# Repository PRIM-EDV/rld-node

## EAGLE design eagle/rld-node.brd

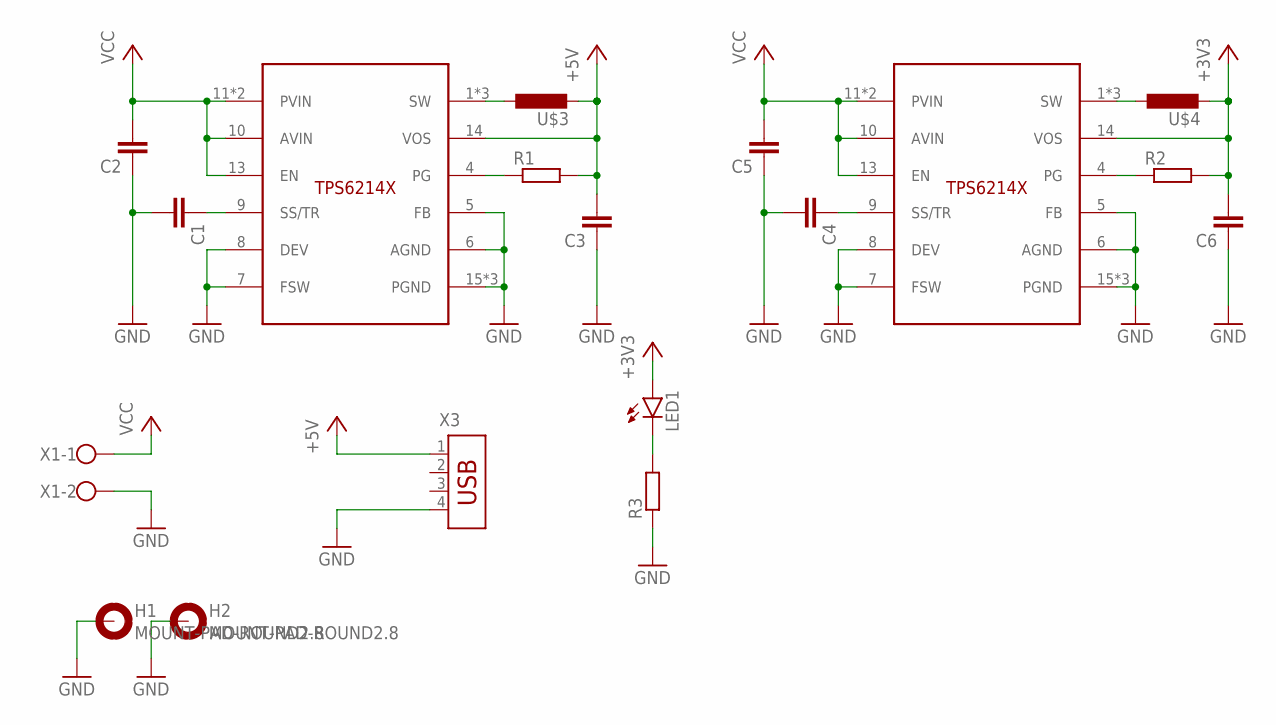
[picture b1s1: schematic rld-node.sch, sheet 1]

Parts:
C1, C2, C3, C4, C5, C6: C-EUC0805; C0805
H1, H2: MOUNT-PAD-ROUND2.8; 2,8-PAD
L1, L2: TPS6214X; VQFN16-3X3
LED1: LEDSML0805; SML0805
R1, R2, R3: R-EU_R0805; R0805
U$3, U$4: IHLP-1212; 1212BZ
X1: W237-102
X3: USB-787616; USB

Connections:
+3V3: C6.2, L2.14 (VOS), LED1.A, R2.2, U$4.2; also elsewhere on the board
+5V: C3.2, L1.14 (VOS), R1.2, U$3.2, X3.1
GND: C1.2, C2.1, C3.1, C4.2, C5.1, C6.1, H1.B2,8, H2.B2,8, L1.5 (FB), L1.6 (AGND), L1.7 (FSW), L1.8 (DEV), L1.15 (PGND), L1.16 (PGND), L1.17 (PGND), L2.5 (FB), L2.6 (AGND), L2.7 (FSW), L2.8 (DEV), L2.15 (PGND), L2.16 (PGND), L2.17 (PGND), R3.1, X1.2, X3.4; also elsewhere on the board
unnamed: C1.1, L1.9 (SS/TR)
unnamed: C4.1, L2.9 (SS/TR)
unnamed: L2.4 (PG), R2.1
unnamed: L1.4 (PG), R1.1
unnamed: L1.1 (SW), L1.2 (SW), L1.3 (SW), U$3.1
unnamed: L2.1 (SW), L2.2 (SW), L2.3 (SW), U$4.1
unnamed: LED1.C, R3.2
VCC: C2.2, C5.2, L1.10 (AVIN), L1.11 (PVIN), L1.12 (PVIN), L1.13 (EN), L2.10 (AVIN), L2.11 (PVIN), L2.12 (PVIN), L2.13 (EN), X1.1

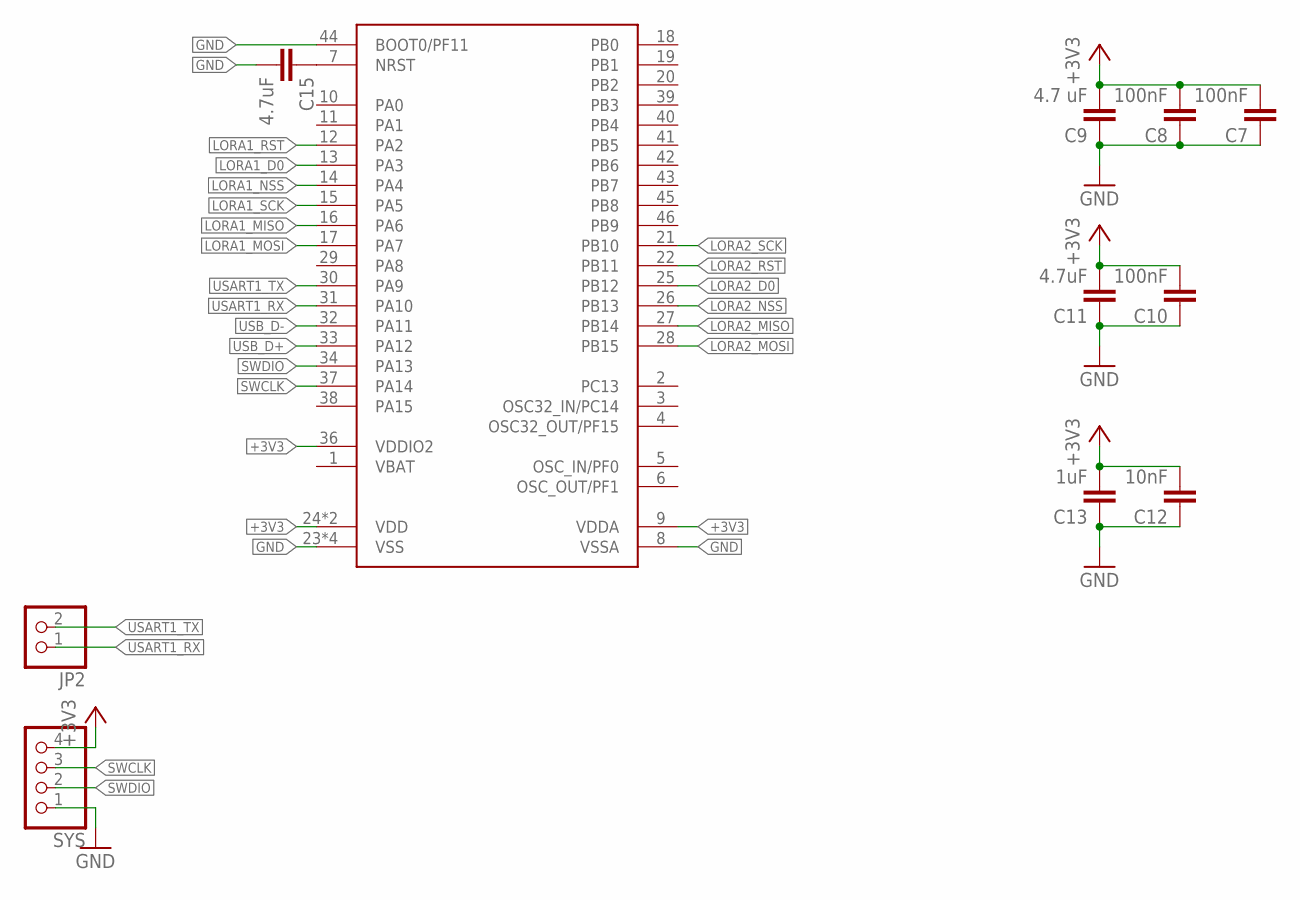
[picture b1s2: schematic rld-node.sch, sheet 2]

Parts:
C7, C8, C10: 100nF; C0805
C9: 4.7 uF; C0805
C11, C15: 4.7uF; C0805
C12: 10nF; C0805
C13: 1uF; C0805
JP2: PINHD-1X2; 1X02
SYS: PINHD-1X4; 1X04
U$5: STM32-F042X4/6-48; UFQFPN48-7X7

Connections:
+3V3: C7.2, C8.2, C9.2, C10.2, C11.2, C12.2, C13.2, SYS.4, U$5.9 (VDDA), U$5.24 (VDD), U$5.36 (VDDIO2), U$5.48 (VDD); also elsewhere on the board
GND: C7.1, C8.1, C9.1, C10.1, C11.1, C12.1, C13.1, C15.2, SYS.1, U$5.8 (VSSA), U$5.23 (VSS), U$5.35 (VSS), U$5.44 (BOOT0/PF11), U$5.47 (VSS), U$5.49 (VSS); also elsewhere on the board
LORA1_D0: U$5.13 (PA3); also elsewhere on the board
LORA1_MISO: U$5.16 (PA6); also elsewhere on the board
LORA1_MOSI: U$5.17 (PA7); also elsewhere on the board
LORA1_NSS: U$5.14 (PA4); also elsewhere on the board
LORA1_RST: U$5.12 (PA2); also elsewhere on the board
LORA1_SCK: U$5.15 (PA5); also elsewhere on the board
LORA2_D0: U$5.25 (PB12); also elsewhere on the board
LORA2_MISO: U$5.27 (PB14); also elsewhere on the board
LORA2_MOSI: U$5.28 (PB15); also elsewhere on the board
LORA2_NSS: U$5.26 (PB13); also elsewhere on the board
LORA2_RST: U$5.22 (PB11); also elsewhere on the board
LORA2_SCK: U$5.21 (PB10); also elsewhere on the board
unnamed: C15.1, U$5.7 (NRST)
SWCLK: SYS.3, U$5.37 (PA14)
SWDIO: SYS.2, U$5.34 (PA13)
USART1_RX: JP2.1, U$5.31 (PA10)
USART1_TX: JP2.2, U$5.30 (PA9)
USB_D+: U$5.33 (PA12)
USB_D-: U$5.32 (PA11)

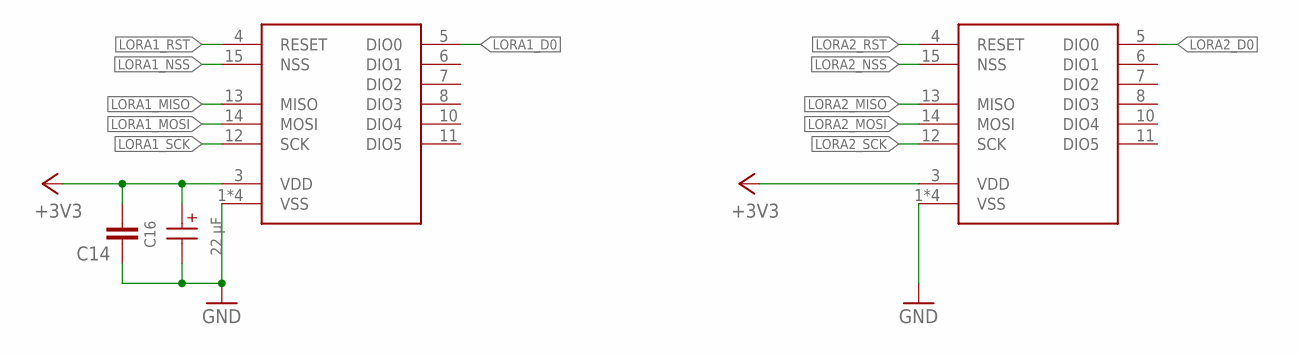
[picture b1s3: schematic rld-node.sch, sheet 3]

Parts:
C14: C-EUC0805; C0805
C16: 22 µF; WCAP-ASLI_4X5.5(DXL)
U$6, U$7: RA-02; RA-01/RA-02

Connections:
+3V3: C14.2, C16.1 (+), U$6.3 (VDD), U$7.3 (VDD); also elsewhere on the board
GND: C14.1, C16.2 (-), U$6.1 (VSS), U$6.2 (VSS), U$6.9 (VSS), U$6.16 (VSS), U$7.1 (VSS), U$7.2 (VSS), U$7.9 (VSS), U$7.16 (VSS); also elsewhere on the board
LORA1_D0: U$6.5 (DIO0); also elsewhere on the board
LORA1_MISO: U$6.13 (MISO); also elsewhere on the board
LORA1_MOSI: U$6.14 (MOSI); also elsewhere on the board
LORA1_NSS: U$6.15 (NSS); also elsewhere on the board
LORA1_RST: U$6.4 (RESET); also elsewhere on the board
LORA1_SCK: U$6.12 (SCK); also elsewhere on the board
LORA2_D0: U$7.5 (DIO0); also elsewhere on the board
LORA2_MISO: U$7.13 (MISO); also elsewhere on the board
LORA2_MOSI: U$7.14 (MOSI); also elsewhere on the board
LORA2_NSS: U$7.15 (NSS); also elsewhere on the board
LORA2_RST: U$7.4 (RESET); also elsewhere on the board
LORA2_SCK: U$7.12 (SCK); also elsewhere on the board

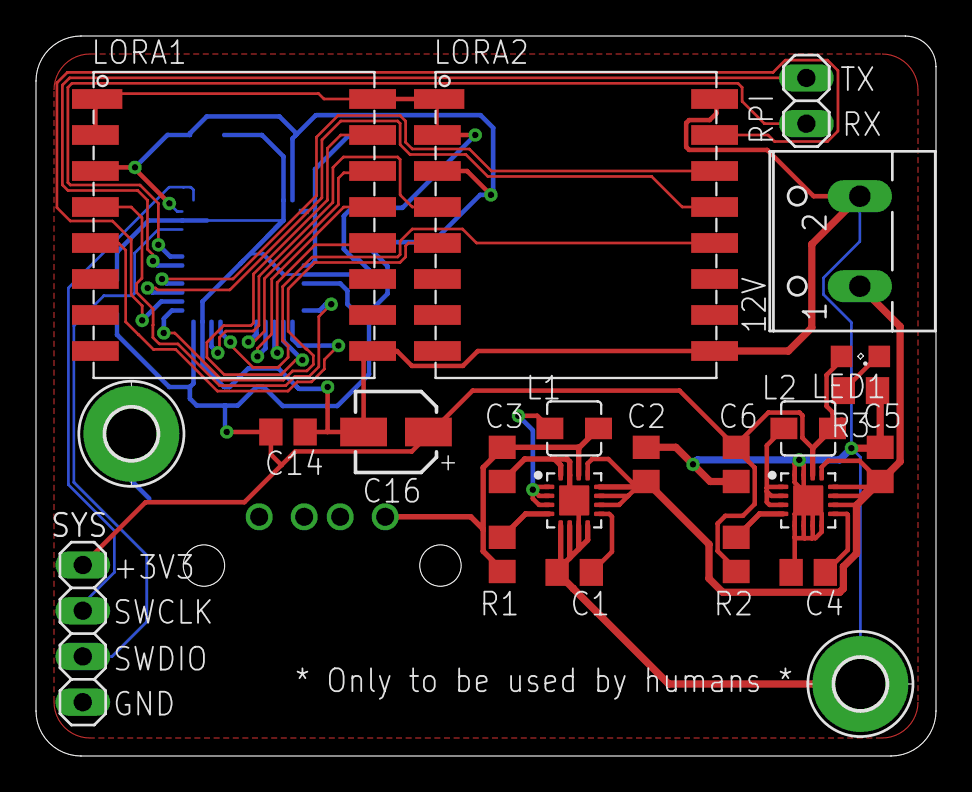
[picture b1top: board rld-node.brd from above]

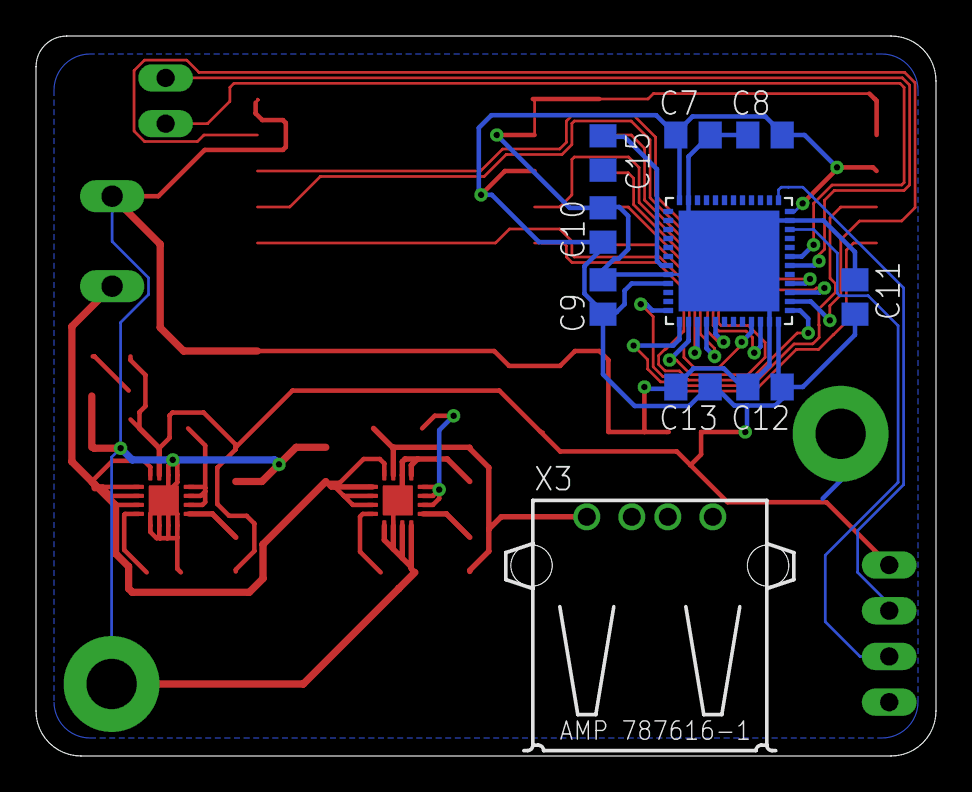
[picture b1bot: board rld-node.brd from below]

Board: 2 copper layers, 50.0 x 40.0 mm, 33 parts (10 on the bottom side), 28 nets.

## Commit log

2020-02-27 Added power supply
2020-06-25 Added synched layout
2020-06-30 Nearly finished design
2020-12-29 Added app boilerplate
2021-05-29 Removed wrong submodule path
2021-05-29 Added modm-boilerplate for firmware
2021-05-29 Added board definition
2021-05-29 added .gitignore and .vscode config
2021-05-29 Fixed spi configuration errors
2021-05-29 Added ai-thinker submodule
2021-05-29 Added nest-js boilerplate and docker configuration
2021-05-29 Bump hosted-git-info from 2.8.8 to 2.8.9 in /rpi/app
    Bumps [hosted-git-info](https://github.com/npm/hosted-git-info) from 2.8.8 to 2.8.9.
    - [Release notes](https://github.com/npm/hosted-git-info/releases)
    - [Changelog](https://github.com/npm/hosted-git-info/blob/v2.8.9/CHANGELOG.md)
    - [Commits](https://github.com/npm/hosted-git-info/compare/v2.8.8...v2.8.9)
2021-05-29 Bump browserslist from 4.16.0 to 4.16.6 in /rpi/app
    Bumps [browserslist](https://github.com/browserslist/browserslist) from 4.16.0 to 4.16.6.
    - [Release notes](https://github.com/browserslist/browserslist/releases)
    - [Changelog](https://github.com/browserslist/browserslist/blob/main/CHANGELOG.md)
    - [Commits](https://github.com/browserslist/browserslist/compare/4.16.0...4.16.6)
2021-05-29 Bump lodash from 4.17.20 to 4.17.21 in /rpi/app
    Bumps [lodash](https://github.com/lodash/lodash) from 4.17.20 to 4.17.21.
    - [Release notes](https://github.com/lodash/lodash/releases)
    - [Commits](https://github.com/lodash/lodash/compare/4.17.20...4.17.21)
2021-05-29 Bump ws from 7.4.2 to 7.4.6 in /rpi/app
    Bumps [ws](https://github.com/websockets/ws) from 7.4.2 to 7.4.6.
    - [Release notes](https://github.com/websockets/ws/releases)
    - [Commits](https://github.com/websockets/ws/compare/7.4.2...7.4.6)
2021-05-30 Started re-implementation of sx127x
2021-05-31 Added implementation
2021-05-31 Updated sx127x
2021-05-31 Fixed missing voltage trace and fixed floating BOOT and NRST
2021-06-02 Added Ra2 interface
2021-06-05 Changed USB socket and added power LED
2021-06-05 Added nanopb protocol buffer repo
2021-06-05 Removed nanopb temporarily
2021-06-05 Re-added nanopb
2021-06-05 made nanopb repo working
2021-06-07 Fixed package vulnerabilities
2021-06-12 Bump glob-parent from 5.1.1 to 5.1.2 in /rpi/app
    Bumps [glob-parent](https://github.com/gulpjs/glob-parent) from 5.1.1 to 5.1.2.
    - [Release notes](https://github.com/gulpjs/glob-parent/releases)
    - [Changelog](https://github.com/gulpjs/glob-parent/blob/main/CHANGELOG.md)
    - [Commits](https://github.com/gulpjs/glob-parent/compare/v5.1.1...v5.1.2)
    ---
    updated-dependencies:
2021-08-13 Bump path-parse from 1.0.6 to 1.0.7 in /rpi/app
    Bumps [path-parse](https://github.com/jbgutierrez/path-parse) from 1.0.6 to 1.0.7.
    - [Release notes](https://github.com/jbgutierrez/path-parse/releases)
    - [Commits](https://github.com/jbgutierrez/path-parse/commits/v1.0.7)
    ---
    updated-dependencies:
    - dependency-name: path-parse
2021-09-22 Bump tmpl from 1.0.4 to 1.0.5 in /rpi/app
    Bumps [tmpl](https://github.com/daaku/nodejs-tmpl) from 1.0.4 to 1.0.5.
    - [Release notes](https://github.com/daaku/nodejs-tmpl/releases)
    - [Commits](https://github.com/daaku/nodejs-tmpl/commits/v1.0.5)
    ---
    updated-dependencies:
    - dependency-name: tmpl
2022-01-15 Bump follow-redirects from 1.14.1 to 1.14.7 in /rpi/app
    Bumps [follow-redirects](https://github.com/follow-redirects/follow-redirects) from 1.14.1 to 1.14.7.
    - [Release notes](https://github.com/follow-redirects/follow-redirects/releases)
    - [Commits](https://github.com/follow-redirects/follow-redirects/compare/v1.14.1...v1.14.7)
    ---
    updated-dependencies:
    - dependency-name: follow-redirects
2022-02-14 Bump follow-redirects from 1.14.1 to 1.14.8 in /rpi/app
    Bumps [follow-redirects](https://github.com/follow-redirects/follow-redirects) from 1.14.1 to 1.14.8.
    - [Release notes](https://github.com/follow-redirects/follow-redirects/releases)
    - [Commits](https://github.com/follow-redirects/follow-redirects/compare/v1.14.1...v1.14.8)
    ---
    updated-dependencies:
    - dependency-name: follow-redirects
2022-06-25 Bump jsdom from 16.4.0 to 16.7.0 in /rpi/app
    Bumps [jsdom](https://github.com/jsdom/jsdom) from 16.4.0 to 16.7.0.
    - [Release notes](https://github.com/jsdom/jsdom/releases)
    - [Changelog](https://github.com/jsdom/jsdom/blob/master/Changelog.md)
    - [Commits](https://github.com/jsdom/jsdom/compare/16.4.0...16.7.0)
    ---
    updated-dependencies:
2022-06-25 Bump node-fetch from 2.6.1 to 2.6.7 in /rpi/app
    Bumps [node-fetch](https://github.com/node-fetch/node-fetch) from 2.6.1 to 2.6.7.
    - [Release notes](https://github.com/node-fetch/node-fetch/releases)
    - [Commits](https://github.com/node-fetch/node-fetch/compare/v2.6.1...v2.6.7)
    ---
    updated-dependencies:
    - dependency-name: node-fetch
2022-07-20 Bump terser from 5.5.1 to 5.14.2 in /rpi/app
    Bumps [terser](https://github.com/terser/terser) from 5.5.1 to 5.14.2.
    - [Release notes](https://github.com/terser/terser/releases)
    - [Changelog](https://github.com/terser/terser/blob/master/CHANGELOG.md)
    - [Commits](https://github.com/terser/terser/commits)
    ---
    updated-dependencies:
2022-07-30 Removed external nanopb
2022-07-30 Bump glob-parent from 5.1.1 to 5.1.2 in /rpi/server/app/app
    Bumps [glob-parent](https://github.com/gulpjs/glob-parent) from 5.1.1 to 5.1.2.
    - [Release notes](https://github.com/gulpjs/glob-parent/releases)
    - [Changelog](https://github.com/gulpjs/glob-parent/blob/main/CHANGELOG.md)
    - [Commits](https://github.com/gulpjs/glob-parent/compare/v5.1.1...v5.1.2)
    ---
    updated-dependencies:
2022-07-30 Bump follow-redirects from 1.14.1 to 1.15.1 in /rpi/server/app/app
    Bumps [follow-redirects](https://github.com/follow-redirects/follow-redirects) from 1.14.1 to 1.15.1.
    - [Release notes](https://github.com/follow-redirects/follow-redirects/releases)
    - [Commits](https://github.com/follow-redirects/follow-redirects/compare/v1.14.1...v1.15.1)
    ---
    updated-dependencies:
    - dependency-name: follow-redirects
2022-07-30 Bump node-fetch from 2.6.1 to 2.6.7 in /rpi/server/app/app
    Bumps [node-fetch](https://github.com/node-fetch/node-fetch) from 2.6.1 to 2.6.7.
    - [Release notes](https://github.com/node-fetch/node-fetch/releases)
    - [Commits](https://github.com/node-fetch/node-fetch/compare/v2.6.1...v2.6.7)
    ---
    updated-dependencies:
    - dependency-name: node-fetch
2022-07-30 Bump jsdom from 16.4.0 to 16.7.0 in /rpi/server/app/app
    Bumps [jsdom](https://github.com/jsdom/jsdom) from 16.4.0 to 16.7.0.
    - [Release notes](https://github.com/jsdom/jsdom/releases)
    - [Changelog](https://github.com/jsdom/jsdom/blob/master/Changelog.md)
    - [Commits](https://github.com/jsdom/jsdom/compare/16.4.0...16.7.0)
    ---
    updated-dependencies:
2022-07-30 Bump ansi-regex from 3.0.0 to 3.0.1 in /rpi/server/app/app
    Bumps [ansi-regex](https://github.com/chalk/ansi-regex) from 3.0.0 to 3.0.1.
    - [Release notes](https://github.com/chalk/ansi-regex/releases)
    - [Commits](https://github.com/chalk/ansi-regex/compare/v3.0.0...v3.0.1)
    ---
    updated-dependencies:
    - dependency-name: ansi-regex
2022-07-30 Bump terser from 5.5.1 to 5.14.2 in /rpi/server/app/app
    Bumps [terser](https://github.com/terser/terser) from 5.5.1 to 5.14.2.
    - [Release notes](https://github.com/terser/terser/releases)
    - [Changelog](https://github.com/terser/terser/blob/master/CHANGELOG.md)
    - [Commits](https://github.com/terser/terser/compare/v5.5.1...v5.14.2)
    ---
    updated-dependencies:
2022-07-30 updated modm
2022-07-30 Bump ansi-regex from 3.0.0 to 3.0.1 in /rpi/server/app
    Bumps [ansi-regex](https://github.com/chalk/ansi-regex) from 3.0.0 to 3.0.1.
    - [Release notes](https://github.com/chalk/ansi-regex/releases)
    - [Commits](https://github.com/chalk/ansi-regex/compare/v3.0.0...v3.0.1)
    ---
    updated-dependencies:
    - dependency-name: ansi-regex
2022-07-30 Bump follow-redirects from 1.13.1 to 1.15.1 in /rpi/server/app
    Bumps [follow-redirects](https://github.com/follow-redirects/follow-redirects) from 1.13.1 to 1.15.1.
    - [Release notes](https://github.com/follow-redirects/follow-redirects/releases)
    - [Commits](https://github.com/follow-redirects/follow-redirects/compare/v1.13.1...v1.15.1)
    ---
    updated-dependencies:
    - dependency-name: follow-redirects
2022-07-30 Bump terser from 5.5.1 to 5.14.2 in /rpi/server/app
    Bumps [terser](https://github.com/terser/terser) from 5.5.1 to 5.14.2.
    - [Release notes](https://github.com/terser/terser/releases)
    - [Changelog](https://github.com/terser/terser/blob/master/CHANGELOG.md)
    - [Commits](https://github.com/terser/terser/compare/v5.5.1...v5.14.2)
    ---
    updated-dependencies:
2022-07-30 Bump glob-parent from 5.1.1 to 5.1.2 in /rpi/server/app
    Bumps [glob-parent](https://github.com/gulpjs/glob-parent) from 5.1.1 to 5.1.2.
    - [Release notes](https://github.com/gulpjs/glob-parent/releases)
    - [Changelog](https://github.com/gulpjs/glob-parent/blob/main/CHANGELOG.md)
    - [Commits](https://github.com/gulpjs/glob-parent/compare/v5.1.1...v5.1.2)
    ---
    updated-dependencies:
2022-07-30 Bump node-fetch from 2.6.1 to 2.6.7 in /rpi/server/app
    Bumps [node-fetch](https://github.com/node-fetch/node-fetch) from 2.6.1 to 2.6.7.
    - [Release notes](https://github.com/node-fetch/node-fetch/releases)
    - [Commits](https://github.com/node-fetch/node-fetch/compare/v2.6.1...v2.6.7)
    ---
    updated-dependencies:
    - dependency-name: node-fetch
2022-07-30 Bump jsdom from 16.4.0 to 16.7.0 in /rpi/server/app
    Bumps [jsdom](https://github.com/jsdom/jsdom) from 16.4.0 to 16.7.0.
    - [Release notes](https://github.com/jsdom/jsdom/releases)
    - [Changelog](https://github.com/jsdom/jsdom/blob/master/Changelog.md)
    - [Commits](https://github.com/jsdom/jsdom/compare/16.4.0...16.7.0)
    ---
    updated-dependencies:
2022-07-31 Updated to new nanopb integration
2022-07-31 Fixed broken ai-thinker submodule
2022-07-31 Moved ai-thinker submodule
2022-07-31 Added rpi uart stream interface
2022-07-31 reworked RA02 integration
2022-08-01 Reworked lora thread handling and added cobs implementation
2022-08-01 moved protofile and added gerber
2022-08-01 Removed scons db
2022-08-01 added protobuf parsing
2022-08-01 Added outstream to lora thread
2022-08-01 Added setting of operation mode
2022-08-07 Added lsfr random generator and uuid
2022-08-07 Replaced sprintf for uuid
2022-08-26 Moved server files
2022-08-26 Setup docker compose
2022-08-27 Added maptool proto and restructured services
2022-08-30 Added maptool connection
2022-08-30 Bump shelljs and @nestjs/cli in /rpi/server
    Bumps [shelljs](https://github.com/shelljs/shelljs) and [@nestjs/cli](https://github.com/nestjs/nest-cli). These dependencies needed to be updated together.
    Updates `shelljs` from 0.8.4 to 0.8.5
    - [Release notes](https://github.com/shelljs/shelljs/releases)
    - [Changelog](https://github.com/shelljs/shelljs/blob/master/CHANGELOG.md)
    - [Commits](https://github.com/shelljs/shelljs/compare/v0.8.4...v0.8.5)
    Updates `@nestjs/cli` from 7.6.0 to 9.1.1
2022-09-03 Added serial port passthrough to docker
2022-09-03 Updated docker ignore for faster build
2022-09-03 Fixed errors in package json and docker-compose
2022-09-03 Fixed various protocol bugs
2022-11-26 Fixed protobuf message creation and encoding

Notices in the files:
parts and their libraries:
Eagle_WCAP-ASLI_rev20a: Copyright: Würth Elektronik
